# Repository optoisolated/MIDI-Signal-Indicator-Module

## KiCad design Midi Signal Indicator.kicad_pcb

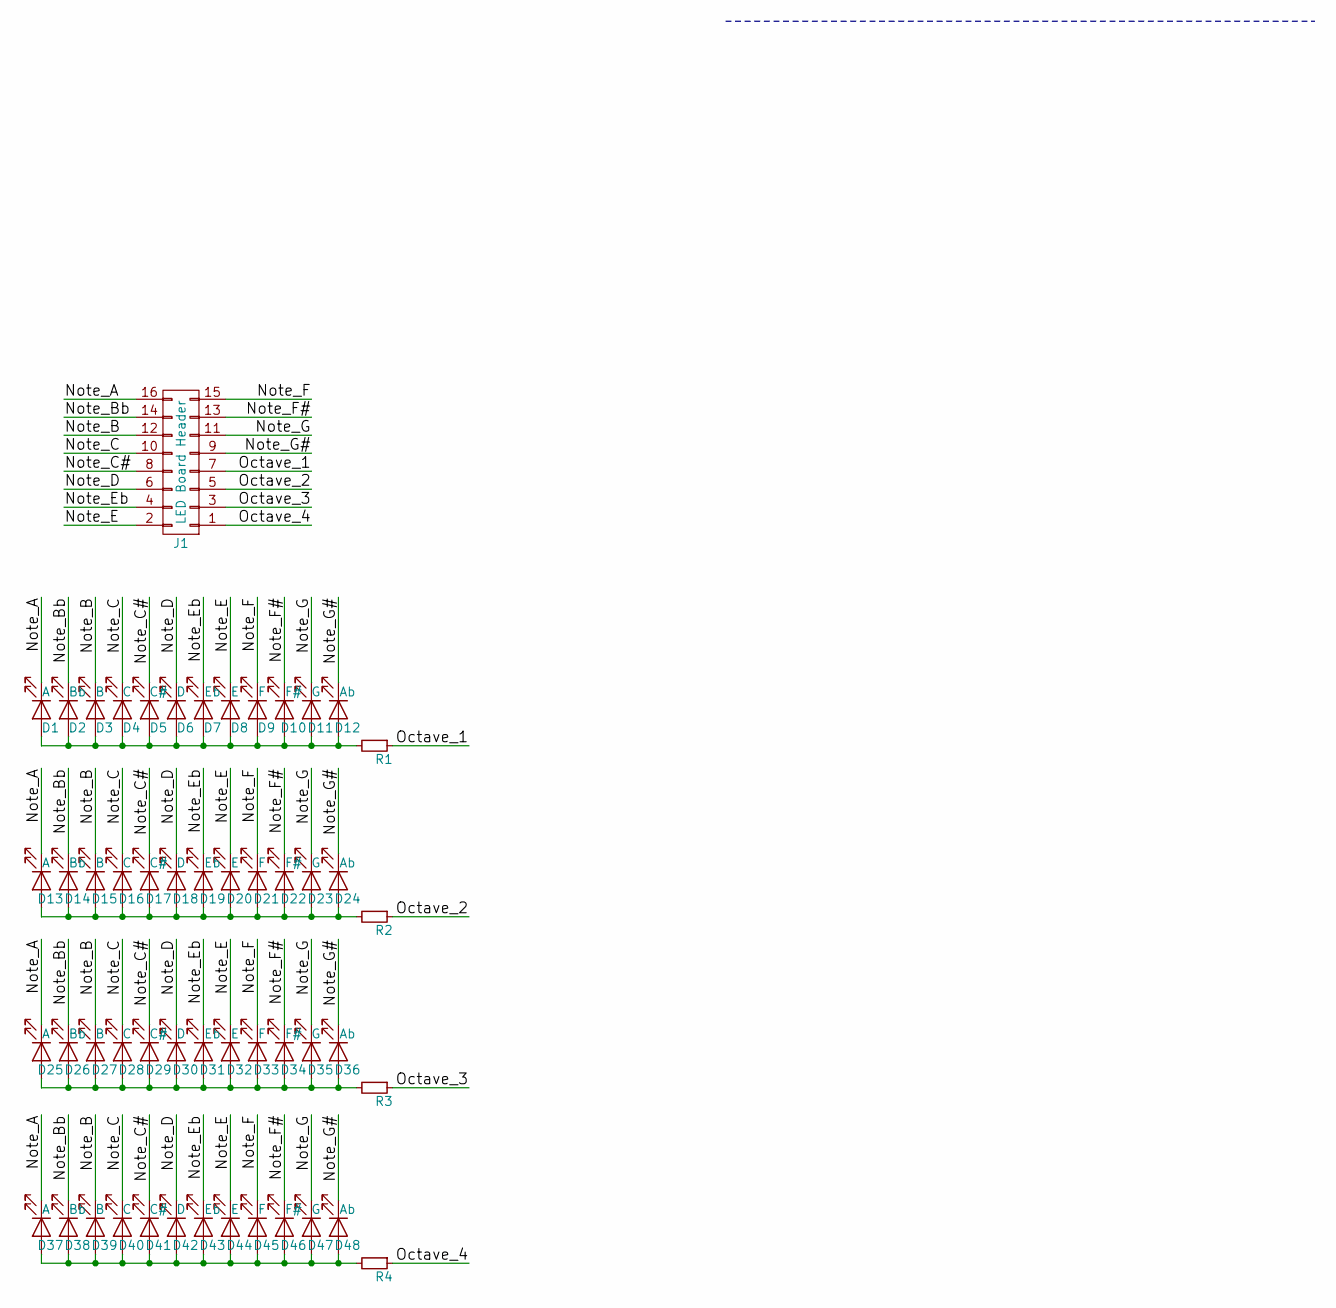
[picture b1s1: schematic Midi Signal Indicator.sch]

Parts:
D1, D13, D25, D37: A; LED_1206
D2, D14, D26, D38: Bb; LED_1206
D3, D15, D27, D39: B; LED_1206
D4, D16, D28, D40: C; LED_1206
D5, D17, D29, D41: C#; LED_1206
D6, D18, D30, D42: D; LED_1206
D7, D19, D31, D43: Eb; LED_1206
D8, D20, D32, D44: E; LED_1206
D9, D21, D33, D45: F; LED_1206
D10, D22, D34, D46: F#; LED_1206
D11, D23, D35, D47: G; LED_1206
D12, D24, D36, D48: Ab; LED_1206
J1: LED Board Header; Pin_Header_Straight_2x08_Pitch2.54mm
R1, R2, R3, R4: 220; R_0603

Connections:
/Note_A: D1.1 (K), D13.1 (K), D25.1 (K), D37.1 (K), J1.16
/Note_B: D3.1 (K), D15.1 (K), D27.1 (K), D39.1 (K), J1.12
/Note_Bb: D2.1 (K), D14.1 (K), D26.1 (K), D38.1 (K), J1.14
/Note_C: D4.1 (K), D16.1 (K), D28.1 (K), D40.1 (K), J1.10
/Note_C#: D5.1 (K), D17.1 (K), D29.1 (K), D41.1 (K), J1.8
/Note_D: D6.1 (K), D18.1 (K), D30.1 (K), D42.1 (K), J1.6
/Note_E: D8.1 (K), D20.1 (K), D32.1 (K), D44.1 (K), J1.2
/Note_Eb: D7.1 (K), D19.1 (K), D31.1 (K), D43.1 (K), J1.4
/Note_F: D9.1 (K), D21.1 (K), D33.1 (K), D45.1 (K), J1.15
/Note_F#: D10.1 (K), D22.1 (K), D34.1 (K), D46.1 (K), J1.13
/Note_G: D11.1 (K), D23.1 (K), D35.1 (K), D47.1 (K), J1.11
/Note_G#: D12.1 (K), D24.1 (K), D36.1 (K), D48.1 (K), J1.9
/Octave_1: J1.7, R1.1
/Octave_2: J1.5, R2.1
/Octave_3: J1.3, R3.1
/Octave_4: J1.1, R4.1
unnamed: D1.2 (A), D2.2 (A), D3.2 (A), D4.2 (A), D5.2 (A), D6.2 (A), D7.2 (A), D8.2 (A), D9.2 (A), D10.2 (A), D11.2 (A), D12.2 (A), R1.2
unnamed: D13.2 (A), D14.2 (A), D15.2 (A), D16.2 (A), D17.2 (A), D18.2 (A), D19.2 (A), D20.2 (A), D21.2 (A), D22.2 (A), D23.2 (A), D24.2 (A), R2.2
unnamed: D25.2 (A), D26.2 (A), D27.2 (A), D28.2 (A), D29.2 (A), D30.2 (A), D31.2 (A), D32.2 (A), D33.2 (A), D34.2 (A), D35.2 (A), D36.2 (A), R3.2
unnamed: D37.2 (A), D38.2 (A), D39.2 (A), D40.2 (A), D41.2 (A), D42.2 (A), D43.2 (A), D44.2 (A), D45.2 (A), D46.2 (A), D47.2 (A), D48.2 (A), R4.2

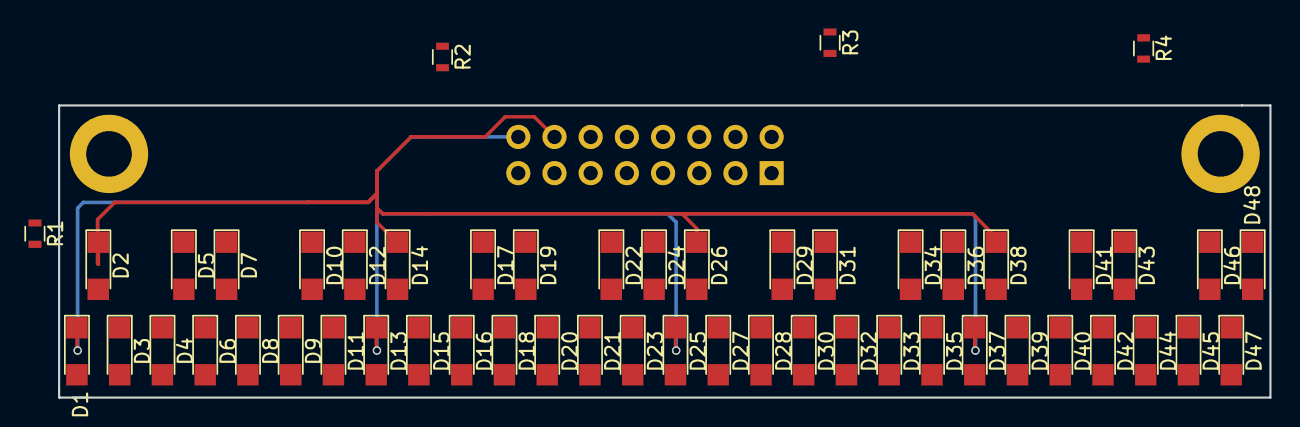
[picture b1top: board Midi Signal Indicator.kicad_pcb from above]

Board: 2 copper layers, 85.0 x 20.5 mm, 53 parts (1 on the bottom side), 20 nets.
